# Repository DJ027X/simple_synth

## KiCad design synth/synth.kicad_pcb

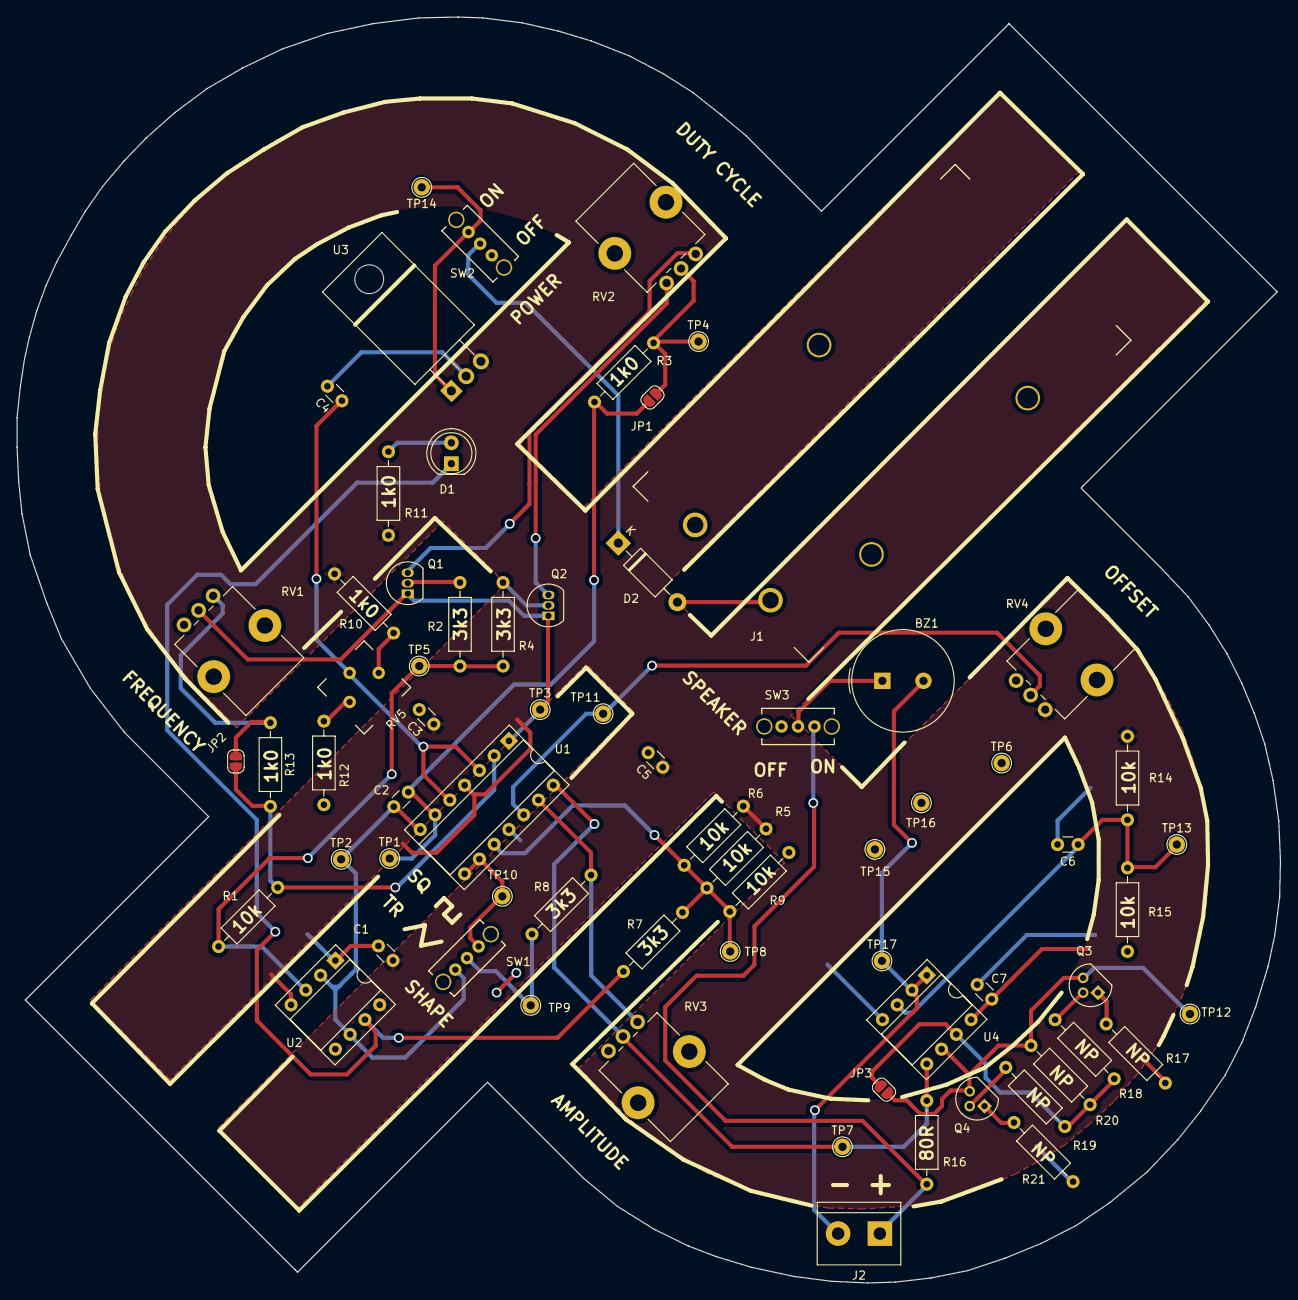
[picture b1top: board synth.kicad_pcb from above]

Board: 2 copper layers, 153.6 x 153.9 mm, 69 parts (0 on the bottom side), 37 nets.

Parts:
BZ1: PASSIVE_BUZZER; Buzzer_TDK_PS1240P02BT_D12.2mm_H6.5mm
C1, C3, C4, C5, C6, C7: 10nF; C_Disc_D3.0mm_W1.6mm_P2.50mm
C2: 100nF; C_Disc_D3.0mm_W1.6mm_P2.50mm
D1: LED; LED_D5.0mm
D2: Diode; D_DO-41_SOD81_P10.16mm_Horizontal
J1: 9V_BAT_HOLDER; BC9VPC
J2: Screw_Terminal_01x02; TerminalBlock_bornier-2_P5.08mm
JP1, JP2: SolderJumper_Open; SolderJumper-2_P1.3mm_Open_RoundedPad1.0x1.5mm
JP3: SolderJumper_Bridged; SolderJumper-2_P1.3mm_Open_RoundedPad1.0x1.5mm
Q1: 2N3904; TO-92_Inline
Q2: 2N3906; TO-92_Inline
Q3: NP_NPN_CBE; TO-92
Q4: NP_PNP_CBE; TO-92
R1, R5, R6, R9, R14, R15: 10k; R_Axial_DIN0207_L6.3mm_D2.5mm_P10.16mm_Horizontal
R2, R4, R7, R8: 3k3; R_Axial_DIN0207_L6.3mm_D2.5mm_P10.16mm_Horizontal
R3, R10, R11, R12, R13: 1k0; R_Axial_DIN0207_L6.3mm_D2.5mm_P10.16mm_Horizontal
R16: 80; R_Axial_DIN0207_L6.3mm_D2.5mm_P10.16mm_Horizontal
R17, R21: NP_47; R_Axial_DIN0207_L6.3mm_D2.5mm_P10.16mm_Horizontal
R18, R19, R20: NP_3k3; R_Axial_DIN0207_L6.3mm_D2.5mm_P10.16mm_Horizontal
RV1, RV2, RV3, RV4: 10k; Potentiometer_Bourns_PTV09A-1_Single_Vertical
RV5: 1k0; CT6EP102
SW1, SW2, SW3: SW_SPDT; OS102011MS2QN1
TP1, TP2, TP3, TP4, TP5, TP6, TP7, TP8, TP9, TP10, TP11, TP12, TP13, TP14, TP15, TP16, TP17: PTH_1_mm; TestPoint_THTPad_D2.0mm_Drill1.0mm
U1: MCP6004; DIP-14_W7.62mm_Socket
U2: SE555P; DIP-8_W7.62mm_Socket
U3: SCD7805BTG; TO-220-3_Horizontal_TabDown
U4: MCP6002; DIP-8_W7.62mm_Socket

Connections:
+5V: C1.1, C3.1, C5.1, C7.1, R5.2, R6.2, R10.1, R11.1, R14.2, R17.1, RV4.1, TP15.1, U1.4, U2.4, U2.8, U3.3, U4.8
/MAIN_VFO/DISCHARGE: D1.1, R7.2, U2.7
/MAIN_VFO/TRIANGLE: C2.1, SW1.1, TP2.1, U1.7, U2.2, U2.6
/MAIN_VFO/TRIM: C4.1, RV5.2, U1.3, U1.5
/OUTPUT/LO_Z_REF: BZ1.2, J2.2, TP17.1, U4.1, U4.2
/OUTPUT/OUTPUT: J2.1, R16.1, SW3.1
GND: C1.2, C3.2, C4.2, C5.2, C6.2, C7.2, J1.2, R9.1, R12.2, R15.1, R21.2, RV4.3, TP6.1, TP16.1, U1.11, U2.1, U3.2, U4.4
HI_Z_REF: C6.1, R14.1, R15.2, TP13.1, U4.3
unnamed: BZ1.1, SW3.2
unnamed: C2.2, JP1.1, R3.1, TP1.1, U1.6
unnamed: D1.2, R11.2
unnamed: D2.1, SW2.2
unnamed: D2.2, J1.1
unnamed: JP1.2, R3.2, RV2.2, TP4.1
unnamed: JP2.1, R13.1, RV1.3
unnamed: JP2.2, R1.2, R13.2, U1.2
unnamed: JP3.1, R18.2, R19.2, R20.2, U4.7
unnamed: JP3.2, Q3.3, Q4.3, R20.1, TP12.1, U4.6
unnamed: Q1.1, Q2.1, RV1.2, TP3.1, U1.1
unnamed: Q1.2, R2.1
unnamed: Q1.3, RV2.1
unnamed: Q2.2, R4.1
unnamed: Q2.3, RV2.3
unnamed: Q3.1, R17.2
unnamed: Q3.2, R18.1
unnamed: Q4.1, R21.1
unnamed: Q4.2, R19.1
unnamed: R1.1, R2.2, R4.2, TP5.1, U2.3
unnamed: R5.1, R6.1, R7.1, R9.2, TP8.1, U1.10
unnamed: R8.1, SW1.2, TP9.1
unnamed: R8.2, RV3.3, U1.13
unnamed: R10.2, RV5.1
unnamed: R12.1, RV5.3
unnamed: RV4.2, TP11.1, U1.12
unnamed: SW1.3, TP10.1, U1.8, U1.9
VDD_BAT: SW2.1, TP14.1, U3.1
VFO_OUT: R16.2, RV3.2, TP7.1, U1.14, U4.5

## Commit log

2020-03-24 automated commit
